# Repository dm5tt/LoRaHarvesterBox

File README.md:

## What is this thing?

This generic LoRa base board is built around the ST STM32WLE5CC (RAK3172) and the TI BQ25570 energy harvester.

It is suitable for a wide range of applications, including:

- Meshtastic (router, sensor) or Meshcore
- LoRaWAN sensors
- Generic raw LoRa devices
- Or virtually any other custom project (ham balloon? Transmitter for tracking penguins?) that utilizes the modulation schemes (FSK, GFSK, MSK, GMSK) of the SX1262

For persistent data storage, an optional FRAM IC (Infineon FM24V10) can be added using I²C. A variety of sensors can additonaly integrated through I²C, SPI (on the back), or USART interfaces.

The power supply design is highly flexible: alongside standard JST-PH connectors, the board also supports very small LiPo batteries (commonly used in in-ear headphones or Bluetooth headsets), which can be soldered directly. Such batteries are readily available on AliExpress (e.g. 501010). The TI BQ25570 also supports exotic storages like Supercaps, LTO, etc.

## Features

### Energy

- Capable of handling a huge variety of energy storages: LiPo, LiFePo4, LTO, SIB, Supercap
- Starts boosting at 600mV. Maximum input voltage is 5.5V. 
- Up to 110mA can be used from the application
- MPPT
- Optional load-switch to switch on/off the entire STM32/LoRa-modem based on the VBAT_OK signal

### Microcontroller

Uses the standardized RAK housing which can house a variety of platforms (ESP32, STM32, etc.) with compatible pins. This variant uses the RAK3172  (ST STM32WLE5CC: 256Kb Flash, 64Kb RAM, 48MHz).

Exposed interfaces:

- 2x USART
- 1x I2C
- 1x SPI (back)
- 2x ADC connected to energy source (like solar) and and energy storage (like LiPos) using voltage dividers
- Multiple break-out pins for GPIOs on the back

### LoRa

Uses the Semtech SX1262 integrated within the STM32 housing. Multiple RAK variants available for 433/470/868/915MHz.

### Data Storage

Infineon FM24V10: 1-MBit non-volatile F-RAM for storing firmware updates, messages or mesurement data

## Design Decisions

### Why did you use the TI BQ25570?

It's the only energy harvester that supports up to 110mA peak current.

I'm not overly happy with this IC as it lacks a few helpful features:

 - No I²C interface and ADC for reading voltages/currents

 - No Thermistor for switching off charging above and below specific temperatures

 - Doesn't switch off VOUT if the battery hits the lower threshold. It only signals it using a pin.

  - Rather annoying pin configuration. Layouting it doesn't make much fun.

 Honestly - It's an old thing compared to the latest generation from ST or e-peas.
  
### Why not buying a "naked" ST STM32WLE5? 

Using a SoC module from RAK brings all the HF and impedancy matching. 

Everything else leaving the housing is not really critical signal wise.

Also it's not too expensive with 6€.

## Hardware

### Pin Configuration

#### ADC

| Signal | Pin | ADC Channel | Info | 
|:--------:|:----:|:-------------:|:------:|
| Energy Storage Voltage | PB3 | A0 | Voltage goes through a Voltage Divider |
| Energy Source Voltage  | PB4 | A1 | Voltage goes through a Voltage Divider |

#### USART

| Peripheral | TX Pin | RX Pin |
|:------------|:--------|:--------|
| UART1 | PB6 | PB7 |
| UART2 | PA2 | PA3 |

#### SWD

| Signal | Pin |
|:--------|:----|
| SWDIO | PA13 |
| SWCLK | PA14 |

##### SPI

| Signal | Pin |
|:--------|:----|
| SPI1, MOSI | PA7 |
| SPI1, MISO | PA6 |
| SPI1, CLK  | PA5 |
| SPI1, NSS  | PA4 |

#### LED

| Signal | Pin |
|:--------|:----|
| LED | PA8 |

#### MISC

| Signal | Pin |
|:--------|:----|
| VBAT_OK from TI BQ25570| PA15 |

### Resistors Values

**Warning:** 

You have to be super careful here. Don't trust your 1%-SMD-Resistor book from Aliexpress or Amazon. Measure each resistor with a high-resolution multimeter and then calculate the voltages according to the readings! A shabby Libreoffice Calc sheet can be found within the `docs` folder to do this.

I wrote a script for calculating proper resistor values here: [ti-bq25570-calculator](https://github.com/h0lad/ti-bq25570-calculator).

## Hardware Verification

### PCB Version v0.0.5

**Power Chain**

✅ 3.3V from TI BQ25570

✅ Charges power storage as defined with R_OV1 and R_OV2

✅ VBAT_OK signal with 3.3V LiPo attached as a storage

✅ Boosts 0.6V to 3.3V without energy storage attached

✅ Lower and upper  VBAT_OK threshold: not testable at the moment. 

✅ Power switch (TI TPS22917DBV) - seems to work. But blocked to to point above.

Findings:
 - The BQ25570 doesn't like my extremely noisy power supply as a storage emulation. It doesn't come up.
 - You have to be very careful as even the tolerance of 1% resistors (R_OV1 and R_OV2) might cause overcharging. So stay away from the hard limits of your battery.

**ST STM32WL55**

✅ Connect to the SWD interface using a ST-Link

## License

CERN Open Hardware Licence Version 2 - Strongly Reciprocal

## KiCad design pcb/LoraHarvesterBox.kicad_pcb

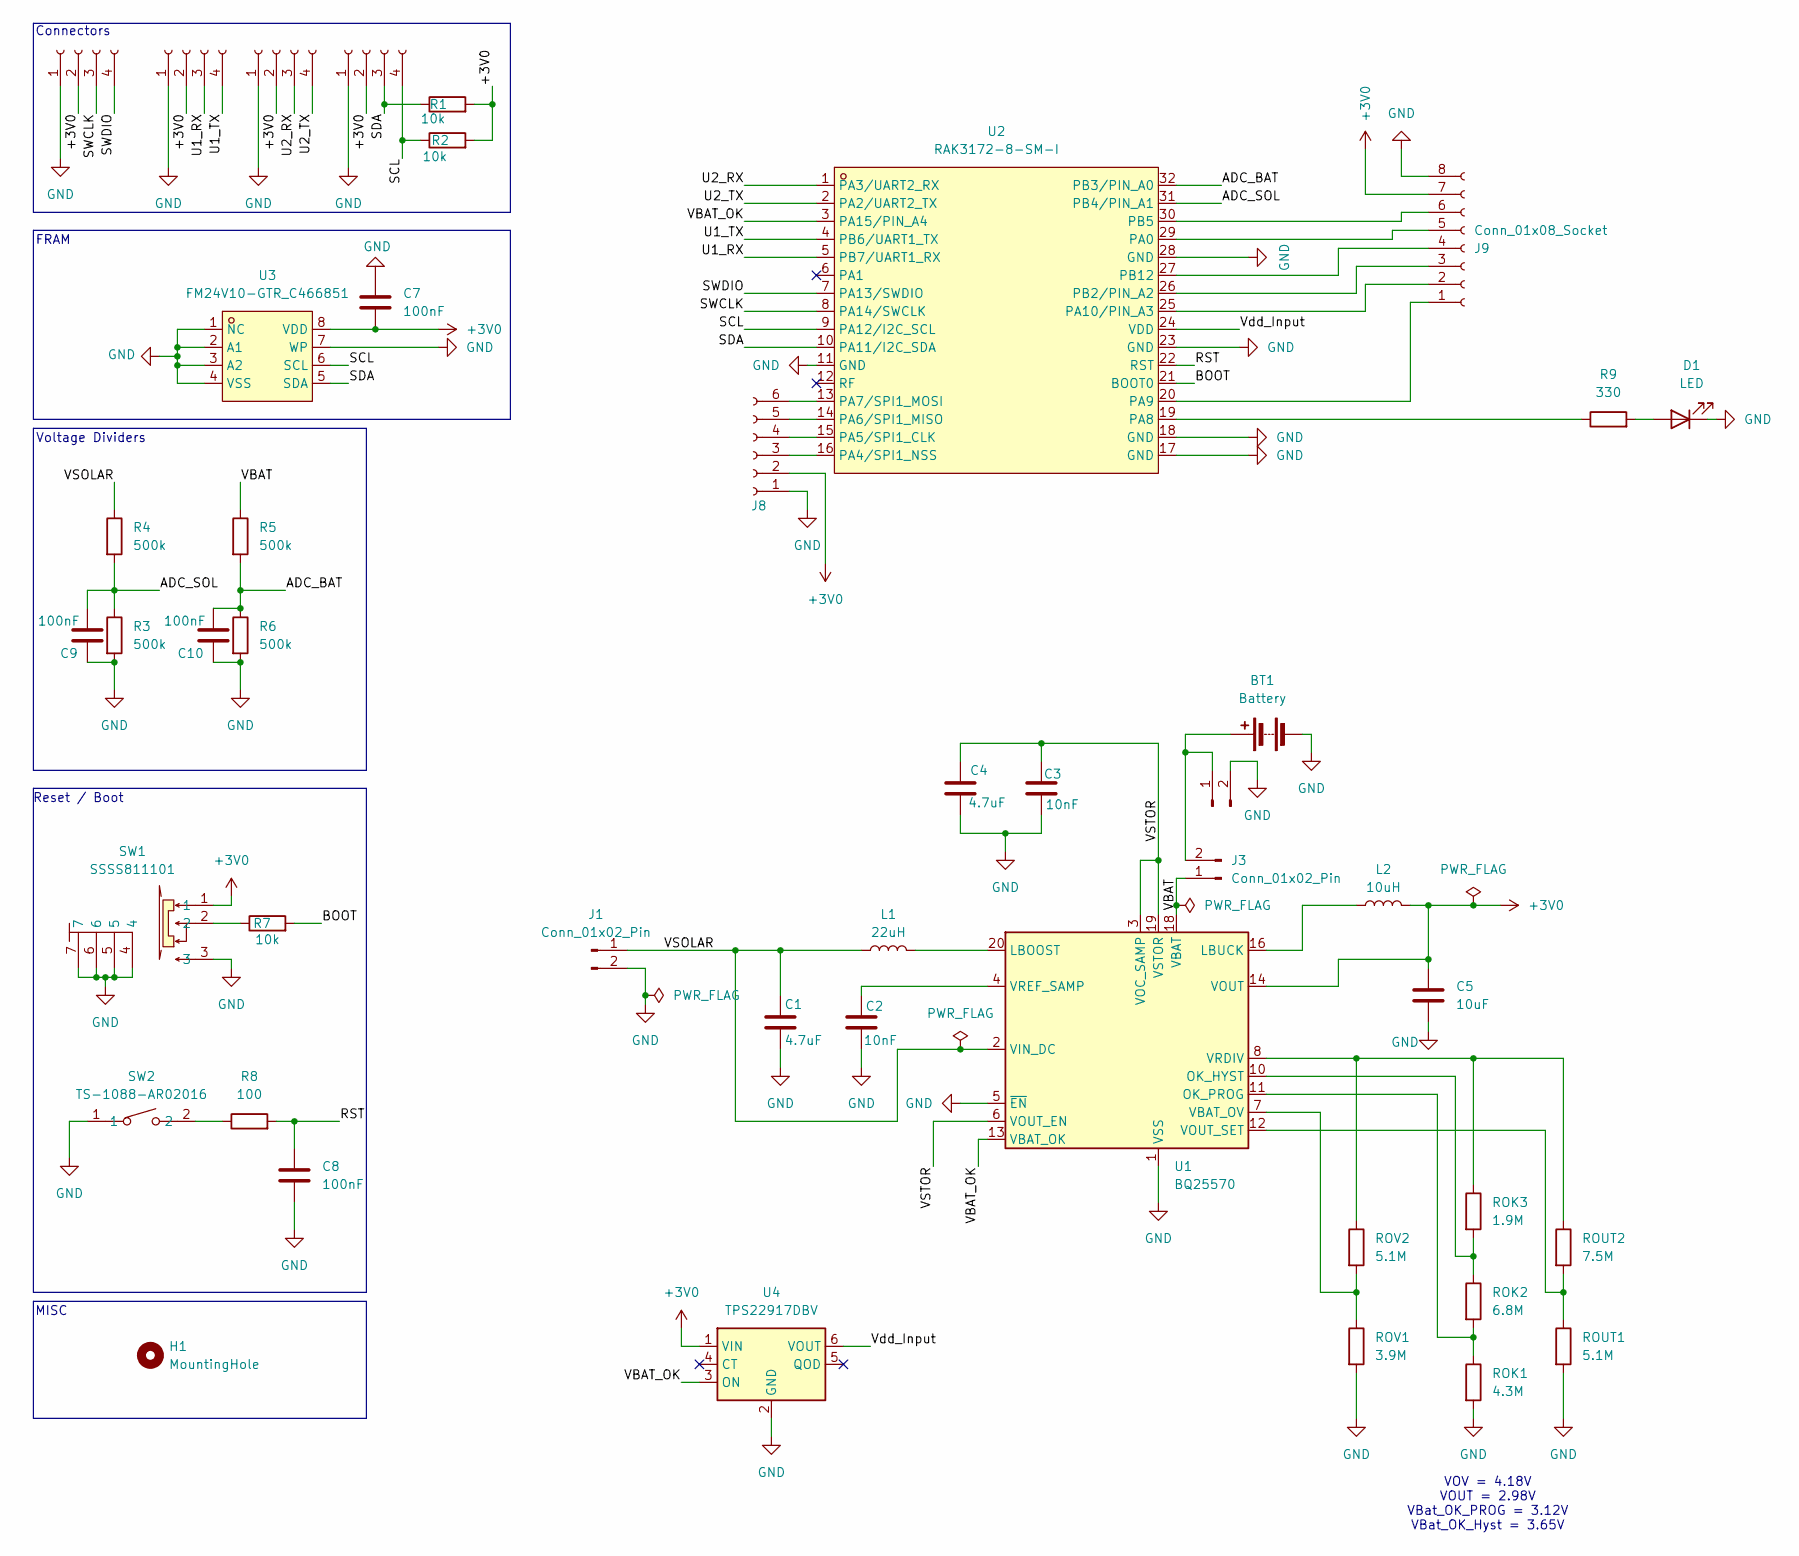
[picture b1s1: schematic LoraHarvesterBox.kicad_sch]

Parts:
BT1: Battery; 501010
C1: 4.7uF; C_0805_2012Metric_Pad1.18x1.45mm_HandSolder
C2, C3: 10nF; C_0603_1608Metric_Pad1.08x0.95mm_HandSolder
C4: 4.7uF; C_0603_1608Metric_Pad1.08x0.95mm_HandSolder
C5: 10uF; C_0805_2012Metric_Pad1.18x1.45mm_HandSolder
C7, C8, C9, C10: 100nF; C_0603_1608Metric_Pad1.08x0.95mm_HandSolder
D1: LED; LED_0603_1608Metric_Pad1.05x0.95mm_HandSolder
H1: MountingHole; MountingHole_2.2mm_M2
J1, J2: Conn_01x02_Pin; JST_PH_B2B-PH-K_1x02_P2.00mm_Vertical
J3: Conn_01x02_Pin; PinHeader_1x02_P2.54mm_Vertical
J4, J5, J6: Conn_01x04_Socket; JST_PH_B4B-PH-K_1x04_P2.00mm_Vertical
J7: Conn_01x04_Socket; JST_ZH_B4B-ZR_1x04_P1.50mm_Vertical
J8: Conn_01x06_Socket; PinHeader_1x06_P1.00mm_Vertical_SMD_Pin1Left
J9: Conn_01x08_Socket; PinHeader_1x08_P1.00mm_Vertical_SMD_Pin1Left
L1: 22uH; L1210
L2: 10uH; L1210
R1, R2: 10k; R_0603_1608Metric
R3, R4, R5, R6: 500k; R_0603_1608Metric_Pad0.98x0.95mm_HandSolder
R7: 10k; R_0603_1608Metric_Pad0.98x0.95mm_HandSolder
R8: 100; R_0603_1608Metric_Pad0.98x0.95mm_HandSolder
R9: 330; R_0603_1608Metric_Pad0.98x0.95mm_HandSolder
ROK1: 4.3M; R_0603_1608Metric_Pad0.98x0.95mm_HandSolder
ROK2: 6.8M; R_0603_1608Metric_Pad0.98x0.95mm_HandSolder
ROK3: 1.9M; R_0603_1608Metric_Pad0.98x0.95mm_HandSolder
ROUT1: 5.1M; R_0603_1608Metric_Pad0.98x0.95mm_HandSolder
ROUT2: 7.5M; R_0603_1608Metric_Pad0.98x0.95mm_HandSolder
ROV1: 3.9M; R_0603_1608Metric_Pad0.98x0.95mm_HandSolder
ROV2: 5.1M; R_0603_1608Metric_Pad0.98x0.95mm_HandSolder
SW1: SSSS811101; SW-SMD_SSSS811101; LCSC Part C109335
SW2: TS-1088-AR02016; SW-SMD_L3.9-W3.0-P4.45; LCSC Part C720477
U1: BQ25570; QFN-20-1EP_3.5x3.5mm_P0.5mm_EP2x2mm
U2: RAK3172-8-SM-I; WIRELM-SMD_32P-L15.5-W15.0-P1.00; LCSC Part C19723904
U3: FM24V10-GTR_C466851; SOIC-8_L5.0-W4.0-P1.27-LS6.0-BL; LCSC Part C466851
U4: TPS22917DBV; SOT-23-6

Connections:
+3V0: C5.2, C7.2, J4.2, J5.2, J6.2, J7.2, J8.2, J9.7, L2.2, R1.2, R2.2, SW1.1, U1.14 (VOUT), U3.8 (VDD), U4.1 (VIN)
/ADC_BAT: C10.2, R5.2, R6.1, U2.32 (PB3/PIN_A0)
/ADC_SOL: C9.2, R3.1, R4.2, U2.31 (PB4/PIN_A1)
/BOOT: R7.2, U2.21 (BOOT0)
/RST: C8.1, R8.2, U2.22 (RST)
/SCL: J7.4, R2.1, U2.9 (PA12/I2C_SCL), U3.6 (SCL)
/SDA: J7.3, R1.1, U2.10 (PA11/I2C_SDA), U3.5 (SDA)
/SWCLK: J4.3, U2.8 (PA14/SWCLK)
/SWDIO: J4.4, U2.7 (PA13/SWDIO)
/U1_RX: J5.3, U2.5 (PB7/UART1_RX)
/U1_TX: J5.4, U2.4 (PB6/UART1_TX)
/U2_RX: J6.3, U2.1 (PA3/UART2_RX)
/U2_TX: J6.4, U2.2 (PA2/UART2_TX)
/VBAT: J3.1, R5.1, U1.18 (VBAT)
/VBAT_OK: U1.13 (VBAT_OK), U2.3 (PA15/PIN_A4), U4.3 (ON)
/VSOLAR: C1.1, J1.1, L1.1, R4.1, U1.2 (VIN_DC)
/VSTOR: C3.1, C4.1, U1.3 (VOC_SAMP), U1.6 (VOUT_EN), U1.19 (VSTOR)
/Vdd_Input: U2.24 (VDD), U4.6 (VOUT)
GND: BT1.2 (-), C1.2, C2.2, C3.2, C4.2, C5.1, C7.1, C8.2, C9.1, C10.1, D1.1 (K), J1.2, J2.2, J4.1, J5.1, J6.1, J7.1, J8.1, J9.8, R3.2, R6.2, ROK1.2, ROUT1.2, ROV1.2, SW1.3, SW1.4, SW1.5, SW1.6, SW1.7, SW2.1, U1.1 (VSS), U1.5 (~EN), U1.9 (VSS), U1.15 (VSS), U1.17 (VSS), U1.21 (VSS), U2.11 (GND), U2.17 (GND), U2.18 (GND), U2.23 (GND), U2.28 (GND), U3.1 (NC), U3.2 (A1), U3.3 (A2), U3.4 (VSS), U3.7 (WP), U4.2 (GND)
unnamed: BT1.1 (+), J2.1, J3.2
unnamed: D1.2 (A), R9.2
unnamed: J8.3, U2.16 (PA4/SPI1_NSS)
unnamed: J8.4, U2.15 (PA5/SPI1_CLK)
unnamed: J8.5, U2.14 (PA6/SPI1_MISO)
unnamed: J8.6, U2.13 (PA7/SPI1_MOSI)
unnamed: J9.1, U2.20 (PA9)
unnamed: J9.2, U2.25 (PA10/PIN_A3)
unnamed: J9.3, U2.26 (PB2/PIN_A2)
unnamed: J9.4, U2.27 (PB12)
unnamed: J9.5, U2.29 (PA0)
unnamed: J9.6, U2.30 (PB5)
unnamed: R7.1, SW1.2
unnamed: R8.1, SW2.2
unnamed: L1.2, U1.20 (LBOOST)
unnamed: L2.1, U1.16 (LBUCK)
unnamed: ROK2.1, ROK3.2, U1.10 (OK_HYST)
unnamed: ROK1.1, ROK2.2, U1.11 (OK_PROG)
unnamed: ROV1.1, ROV2.2, U1.7 (VBAT_OV)
unnamed: ROUT1.1, ROUT2.2, U1.12 (VOUT_SET)
unnamed: ROK3.1, ROUT2.1, ROV2.1, U1.8 (VRDIV)
unnamed: C2.1, U1.4 (VREF_SAMP)
unnamed: R9.1, U2.19 (PA8)

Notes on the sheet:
MISC
Connectors
Reset / Boot
VOV = 4.18V VOUT = 2.98V VBat_OK_PROG = 3.12V VBat_OK_Hyst = 3.65V
Voltage Dividers
FRAM

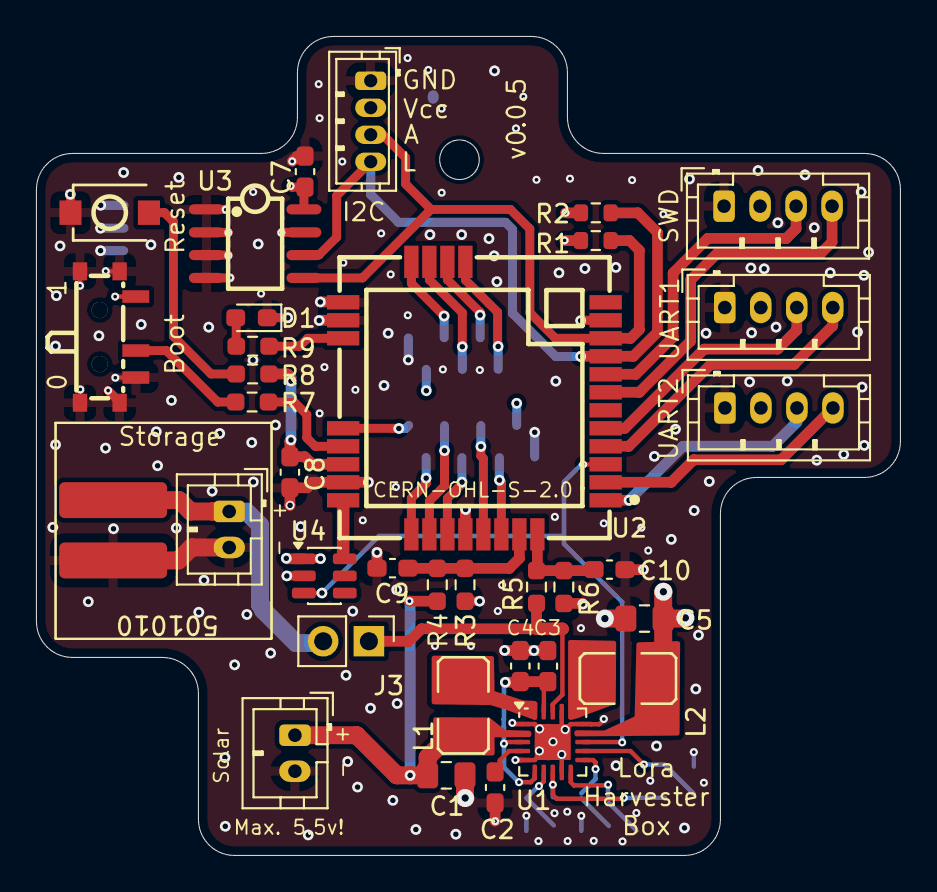
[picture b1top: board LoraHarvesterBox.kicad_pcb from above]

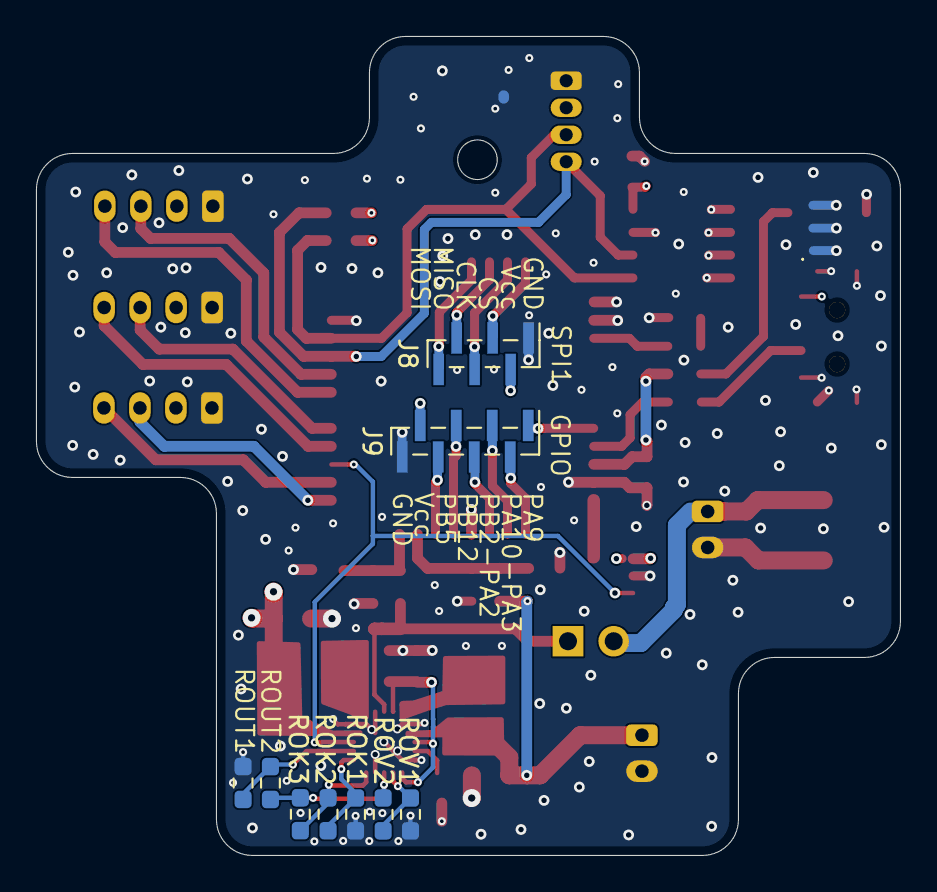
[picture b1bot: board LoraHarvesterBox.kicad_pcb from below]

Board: 4 copper layers, 48.0 x 45.5 mm, 45 parts (9 on the bottom side), 42 nets.

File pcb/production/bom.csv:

Designator,Footprint,Quantity,Value,LCSC Part #
BT1,501010,1,Battery,
C1,0805,1,4.7uF,
C2,0402,1,10nF,
C3,0402,1,0.01uF,
C4,0603,1,4.7uF,
C5,0805,1,10uF,
"C6, C7",0805,2,C,
C8,0402,1,C,
D1,0603,1,LED,
"J1, J2",JST_PH_B2B-PH-K_1x02_P2.00mm_Vertical,2,Conn_01x02_Pin,
J3,PinHeader_1x02_P2.54mm_Vertical,1,Conn_01x02_Pin,
"J4, J5, J6, J7",JST_PH_B4B-PH-K_1x04_P2.00mm_Vertical,4,Conn_01x04_Socket,
J8,PinHeader_1x06_P1.00mm_Vertical_SMD_Pin1Left,1,Conn_01x06_Socket,
L1,L1210,1,22uH,
L2,L1210,1,10uH,
"R1, R2, R7",0603,3,10k,
"R3, R4, R5, R6",0603,4,500k,
R8,0603,1,100,
R9,0603,1,330,
ROK1,0603,1,4.3M,
ROK2,0603,1,6.8M,
ROK3,0603,1,1.9M,
ROUT1,0603,1,5.1M,
ROUT2,0603,1,7.5M,
ROV1,0603,1,3.9M,
SW1,SW-SMD_SSSS811101,1,SSSS811101,C109335
SW2,SW-SMD_L3.9-W3.0-P4.45,1,TS-1088-AR02016,C720477
U1,QFN-20-1EP_3.5x3.5mm_P0.5mm_EP2x2mm,1,BQ25570,
U2,WIRELM-SMD_32P-L15.5-W15.0-P1.00,1,RAK3172-8-SM-I,C19723904
U3,SOIC-8_L5.0-W4.0-P1.27-LS6.0-BL,1,FM24V10-GTR_C466851,C466851

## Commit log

2025-09-06 README: improve chapter about sources
2025-09-06 README: be more precise about the type
2025-09-06 README: add design decisions
2025-09-06 README: 3.0V design decision
2025-09-06 pcb: reannotate as the ROK names jumped around (1->3->2)
2025-09-06 docs, sch, pcb: yes.. now we lost schematic<->datasheet sync. fix annotation
2025-09-06 README: sources -> storages
2025-09-13 pcb, sch: add resistor values and pretty up the pcb a bit
2025-09-13 README: remove stray symbol
2025-09-13 README: harmonize tables
2025-09-13 README: even more clean up of the tables
2025-09-13 README: move tables around one more time
2025-09-13 README: cleanups
2025-09-13 README: add LTO calculations
2025-09-13 README: update voltage tables
2025-09-14 README: add LiFePo4 resistor values
2025-09-14 pcb, sch: connect VBAT_OK signal to mirocontroller
2025-09-19 pcb, sch, doc: replace all 402 components with 0603 or 0805.
    I cannot solder 0402 in my homelab :-( It starts with the mis-aligned tweezers
    and ends with shaking hands.
2025-09-19 sch: remove stray label
2025-09-19 pch, sch: use 0805 capacitor for FRAM and not 0402
2025-09-19 pcb: eye candy changes
2025-09-20 pcb: re-align voltage dividers a bit
2025-09-20 pcb: move silk screens and jumper around
2025-10-03 pcb, sch, doc: remove remaining 0401
2025-10-03 pcb, sch, doc: add buffer C for voltage dividers
2025-10-03 doc: update picture
2025-10-03 pcb, sch, doc: remove C as RAK31762 has 10uF+100nF already internally
2025-10-03 pcb, sch, doc: make more pins available on the back
2025-10-03 sch, pcb, doc: remove FRAM to the top layer
2025-10-03 doc: update documentation
2025-10-03 docs: update back picture
2025-10-03 sch, doc: make I2C connector JST-ZH, move mounting hole
2025-10-03 pcb, doc: keep the area of the mounting hole free
2025-10-03 sch, pcb: clean up BOM
2025-10-03 pcb: add JLCPCB order list
2025-10-03 pcb: fix jclcpb bom list (do not populate BQ25570 resistors and battery)
2025-10-03 pcb: uploaded broken file by accident
2025-10-04 README: add informations regarding downsides
2025-10-04 pcb, doc: improve silk prints of I2C connector
2025-10-04 pcb: update jlcpcb components
2025-10-04 README: advice regarding its age
2025-10-06 README: typos
2025-10-12 pcb, doc, sch: add load switch. VBAT_OK (optionally) can switch on/off the RAK3172
2025-10-12 pcb, prl: add missing gnd connection
2025-10-14 pcb: add missing connection to gnd
2025-10-14 README: rework documentation a bit
2025-10-14 README: remove repeater from Meshtastic and add Meshcore
2025-10-14 README: mention the penguins
2025-10-14 README: must mention the penguin
2025-10-14 README: tidy of pin descriptions
2025-10-14 README: add picture of front pin configuration
2025-10-14 docs: add picture
2025-10-14 pcb, doc: add rendering of JST ZH connector
2025-10-14 doc: replace pictures
2025-10-25 README: add note regarding hardware verification
2025-10-25 README: it's Hardware Verification
2025-10-25 README: move up one chapter
2025-10-26 README: 3v0 vs 3v3 isn't a factor anymore - no LDO left in this design
2025-10-29 github: check pcb using cicd
2025-10-29 github: first cicd attempt for checking kicad errors
2025-10-29 github: force refresh system packager mirrors and packages
2025-10-29 github: use more recent version of kicad
2025-10-29 github: next attempt
2025-10-29 github: kibot takes more time to set it up. spare this for the winter.
2025-11-01 README: add info to ADC voltages
2025-11-05 README: add v0.0.5 hardware verification
2025-11-05 pcb: add missing step files
2025-11-05 cicd: no cicd for now
2025-11-05 README: add missing word
2025-11-05 README: fix invonsistent voltage postfix
2025-11-07 README: be more correct about the input voltages
2025-11-07 README: add warning
2025-11-08 README: looking at you Amazon and Aliexpress
2025-11-08 README: be even more precise about the resistors!
2025-11-08 README: Formatting
2025-11-17 README: add link to ti-bq-25570-calculator for calculating R's
2025-11-17 README: final tests successful

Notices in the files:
pcb/LoraHarvesterBox.kicad_pcb:
CERN-OHL-S-2.0
